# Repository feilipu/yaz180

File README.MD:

# YAZ180

There needed to be <strong>Yet Another Z180</strong> computer created.<br>
And so, here it is.

<div>
<table style="border: 2px solid #cccccc;">
<tbody>
<tr>
<td style="border: 1px solid #cccccc; padding: 6px;"></td>
</tr>
<tr>
<th style="border: 1px solid #cccccc; padding: 6px;"><centre>YAZ180 Version 2.4 2019 Left<center></th>
</tr>
<tr>
<td style="border: 1px solid #cccccc; padding: 6px;"></td>
</tr>
<tr>
<th style="border: 1px solid #cccccc; padding: 6px;"><centre>YAZ180 Version 2.4 2019 Right<center></th>
</tr>
<tr>
<td style="border: 1px solid #cccccc; padding: 6px;"></td>
</tr>
<tr>
<th style="border: 1px solid #cccccc; padding: 6px;"><centre>YAZ180 Version 2.1 2017 Live with YABIOS and CP/M<center></th>
</tr>
</tbody>
</table>
</div>

The [YAZ180](https://feilipu.me/?s=yaz180) is a modern single board computer, built on the tradition rich Z180 CPU and the AMD Am9511A-1 APU.

It is my attempt to create a perfect mix of "ancient" and  modern computing technology. Specifically, it is an attempt to marry CPU/APU technology from 40 years ago, with modern I2C, USB, and WiFi capabilities, and make an powerful 8-bit computer that can either be embedded into an application, or operate as a stand-alone computer (with some accessories).

The YAZ180 is supported by the Z88dk and it is designed to work with both traditional CP/M v2.2 applications and modern Z88dk C compiled programs.

The YAZ180 is fully open source. All documentation and design is available from this repository. I have made the raw PCBs available on [Tindie](https://www.tindie.com/products/feilipu/yaz180-pcb-modern-single-board-z180-computer/). I will find a way to get finished YAZ180 computers available shortly.

## Concept

The Z180 CPU is based on the Z80 CPU, but it includes a number of integrated peripherals including a basic Memory Management Unit (MMU), two serial interfaces (ASCI0 & ASCI1), two DMA controllers (DMAC0 & DMAC1), and two Programmable Reload Timers (PRT0 & PRT1).

The fastest readily available Flash memory is 55ns. This is matched by the fastest RAM in 8 x 1MByte packaging at 45ns. Using these two timings the fastest clock that can be therefore be supported is approximately 20MHz. Using this as a guide, and knowing that the Z180 ASCI interfaces are happiest running at a magic frequency, I have therefore selected 18.432MHz as the crystal oscillator frequency for the YAZ180.

The Z180 can operate internally at 2x the crystal oscillator frequency, which means that the YAZ180 is configured to run with PHI at 36.864MHz with 1 wait memory wait state in normal situations. This is slightly outside the Z180 specification (33MHz), but this frequency is reported to work without issues by a number of SBC builds.

The AMD Am9511A (1977) was the first hardware arithmetic Floating Point Unit (FPU) developed. It is essentially a "scientific calculator" on a chip, and is capable of both 16 bit and 32 bit fixed and 32 bit floating point processing, across all the standard and trancendental functions. Even though this device is 40 years old, it is still [comparable in performance](https://feilipu.me/2017/02/22/characterising-am9511a-1-apu/) of mathematical calculations to its Z180 host.

In addition to the internal Z180 interfaces, I have added a 82C55 Programmable Peripheral Interface (PPI) Controller (1974). This device provides 3x 8 bit parallel ports, and enables the YAZ180 to support 16bit IDE hard drives, as well as providing a mechanism to add parallel data interfacing to future expansion boards.

As the IDE interface requires control signals that are active low, several of the PPI Port C lines are passed through inverters. Importantly, those Port C lines that can accept input in PPI Mode 1 or Mode 2 are not inverted, and are therefore available as inputs from off-board applications. The IDE physical interface cable also provides a tidy board extension format, to allow extension or accessory devices to be attached to the YAZ180.

A single step circuitry has been implemented, which is enabled by a switch, and triggered by writing to an I/O port address. This enables the YAZ180 to run normally, until it becomes interesting to enable a breakpoint.

To interface with modern sensors and devices, two separate I2C interface PCA9665 devices have been provided. This enables one I2C device to be running at 1MHz in Fast-mode Plus (or even Turbo mode) driving a LCD controller for a screen (for example FTDI EVE), and have the other I2C interface connected over longer distances to sensors or keyboard running at 100kHz in Standard mode. The PCA9665 has deep 68 byte hardware buffers, and can operate in buffered or streaming mode, enabling complete I2C sentences to be transmitted or received without CPU interaction. A complete GL graphics command could be sent with one CPU DMA, for example.

To interface with TCP/IP networks, using WiFi, an ESP8266 pin-out for the ESP-01S is provided, connected to ASCI1. This enables the YAZ180 to operate as an Internet server (with attached IDE hard drive), and / or to be controlled using Secure Shell from anywhere.

A USB parallel interface is provided to enable "tool-less" programming of the YAZ180. A perl script is provided to upload Intel HEX code and program it into the system Flash memory. To enable this feature hardware is provided to reconfigure the memory map to allow boot from USB.

## PCB

The YAZ180 PCB is 160mm x 100mm in size, with 4 layers.<br>
This is the maximum size supported by the Eagle "Hobby Licence", which was used to create the PCB.

- Layer Top - all active devices (RED) - 2oz copper
- Layer 2 - GND layer (flood fill) - 0.5oz copper
- Layer 15 - VCC layer (flood fill) - 0.5oz copper
- Layer Bottom - signal traces (BLUE) - 2oz copper

- PCB Dimension - 160mm*100mm
- Material - FR-4 TG130
- Surface Finish - ENIG
- Min Solder Mask Dam - 0.4mm
- PCB Color - Black

<div>
<table style="border: 2px solid #cccccc;">
<tbody>
<tr>
<td style="border: 1px solid #cccccc; padding: 6px;"></td>
</tr>
<tr>
<th style="border: 1px solid #cccccc; padding: 6px;"><centre>YAZ180 Version 2.4 PCB 2019 Layout<center></th>
</tr>
<tr>
<td style="border: 1px solid #cccccc; padding: 6px;"></td>
</tr>
<tr>
<th style="border: 1px solid #cccccc; padding: 6px;"><centre>YAZ180 Version 2.1 PCB 2017<center></th>
</tr>
</tbody>
</table>
</div>

The YAZ180 requires 15V to 40V, 2A power supply, through a standard 2.1mm barrel jack.<br>
If you are not equipping the Am9511A-1 APU, then the minimum required supply voltage drops to 7V.

The main supply is switchmode rated at 5V 3A, which is used by most of the traditional devices on the board. Note that the <strong>TIL-311</strong> LED display devices consume approximately 105mA each, and operate <strong>HOT TO TOUCH</strong>.

A 3.3V 1A rated linear supply is fed from the 5V internal source. 3.3V is needed to support the I2C and ESP-01S devices.

The internal 12V 500mA rated switchmode supply is generated only to support the APU. Note that the <strong>Am9511A-1</strong> consumes 5V 70mA plus 12V 70mA normally, and operates <strong>BURNING HOT TO TOUCH</strong> (seriously).

The Z180 is supported by an ABT logic signal buffer on the /RD, /WR, /MREQ, and /IORQ lines, together with the four lowest address lines, A3, A2, A1, and A0. These signals are provided to all active elements, and so even though the Z180 includes its own signal buffers, I thought these signals should be additionally buffered.

The Z180 data lines are also buffered by an ABT logic bus transceiver. This is to ensure that these lines are also optimally driven.

## BOM

The <a href="https://github.com/feilipu/yaz180/blob/master/docs/YAZ180_V23_ListByValues.csv" target="_blank">Bill of Material</a> is available from DigiKey by modifying this [Shopping Cart](https://www.digikey.com.au/short/j103pz).

Note that there are two significant items missing from the Shopping Cart.

- The <a href="https://github.com/feilipu/yaz180/blob/master/docs/datasheets/Am9511%20Arithmetic%20Processor.pdf" target="_blank">Am9511A-1</a> is obsolete, and is only available from second tier chip sellers.
- The <a href="https://github.com/feilipu/yaz180/blob/master/docs/datasheets/til311.pdf" target="_blank">TIL-311</a> is not obsolete, but is no longer used in modern development and so is also not generally available.

Both of these products are readily available from second tier sources, but due to their scarcity they are not inexpensive.

Some other smaller pin-outs and connectors are not included:

- 2 of Seeed Studio Grove I2C connectors

## Memory & I/O Address Layout

The physical address mapping is provided by the standard CUPL (described below), and is completely arbitrary. Any other CUPL definitions can be programmed into the GAL16V8D "Memory" device to provide any memory layout desired.

### Physical Memory Address Space

The basic layout is to allow for an initial boot from flash memory into a BANK_0, with additional BANK_1 through BANK14 containing 64kB RAM based application spaces. The upper 4kB of each application space will be masked by COMMON AREA 1 RAM, which provides system utilities.

The additional flash memory is assigned to the upper memory space (BANK13, BANK14, and) BANK15, depending on the size of flash storage equipped. This non-volatile storage can be used for any purpose.

The PROGRAMMING MODE hardware recognises that data is available on the USB parallel port, and reconfigures the physical address mapping to enable boot from USB, and further programming of Flash or RAM.

<div>
<table style="border: 2px solid #cccccc;">
<tbody>
<tr>
<th style="border: 2px solid #cccccc; padding: 6px;">Physical Address Range</th>
<th style="border: 2px solid #cccccc; padding: 6px;">Run Mode</th>
<th style="border: 2px solid #cccccc; padding: 6px;">Programming Mode</th>
</tr>
<tr>
<th style="border: 1px solid #cccccc; padding: 6px;">$00000 - $0BFFF</th>
<td style="border: 1px solid #cccccc; padding: 6px;">Flash (48kB of 128kB)</td>
<td style="border: 1px solid #cccccc; padding: 6px;">USB pseudo RAM (48kB)</td>
</tr>
<tr>
<th style="border: 1px solid #cccccc; padding: 6px;">$0C000 - $DFFFF</th>
<td style="border: 1px solid #cccccc; padding: 6px;">SRAM (848kB of 1MB)</td>
<td style="border: 1px solid #cccccc; padding: 6px;">SRAM (848kB of 1MB)</td>
</tr>
<tr>
<th style="border: 1px solid #cccccc; padding: 6px;">$E0000 - $EFFFF</th>
<td style="border: 1px solid #cccccc; padding: 6px;">SRAM (64kB of 1MB)</td>
<td style="border: 1px solid #cccccc; padding: 6px;">Flash (64kB of 128kB)</td>
</tr>
<tr>
<th style="border: 1px solid #cccccc; padding: 6px;">$F0000 - $FFFFF</th>
<td style="border: 1px solid #cccccc; padding: 6px;">Flash (64kB of 128kB)</td>
<td style="border: 1px solid #cccccc; padding: 6px;">Flash (64kB of 128kB)</td>
</tr>
</tbody>
</table>
</div>

### Logical Memory Address Space

There is no need to follow this logical address space mapping. This is what I prefer. You can do whatever you want.

The organisation below is an attempt to provide a BANK_0 containing YABIOS (CRT0, boot code, and Z88dk library code) together with a RAM system heap. The COMMON AREA 1 space from 0xF000 to 0xFFFF is intended to hold banking code, system call forwarding, interrupt service routines, system buffers, and a system stack.

Additional BANK_1 through BANK14 are intended to hold user code, whether CP/M or Z88dk C programs, both are supported through system calls to BANK_0.

Flash found in (BANK13, BANK14, and) BANK15 is intended to be used for snapshots of default or frequently used applications. For example a CP/M snapshot would enable a "diskless" CP/M initialisation, using DMA to load within fractions of a second. Suggested default snapshots could be: CP/M CCP/BDOS, CP/M + BASIC, or Webserver, for example.

<div>
<table style="border: 2px solid #cccccc;">
<tbody>
<tr>
<th style="border: 2px solid #cccccc; padding: 6px;">Logical Address Range</th>
<th style="border: 2px solid #cccccc; padding: 6px;">Run Mode</th>
<th style="border: 2px solid #cccccc; padding: 6px;">Programming Mode</th>
</tr>
<tr>
<th style="border: 1px solid #cccccc; padding: 6px;">$0000 - $BFFF</th>
<td style="border: 1px solid #cccccc; padding: 6px;">Flash (48kB, BANK_0)</td>
<td style="border: 1px solid #cccccc; padding: 6px;">USB (48kB, CA0)</td>
</tr>
<tr>
<th style="border: 1px solid #cccccc; padding: 6px;">$C000 - $EFFF</th>
<td style="border: 1px solid #cccccc; padding: 6px;">SRAM (12kB, BANK_0)</td>
<td style="border: 1px solid #cccccc; padding: 6px;">Flash (8kB, BANK)</td>
</tr>
<tr>
<th style="border: 1px solid #cccccc; padding: 6px;">$F000 - $FFFF</th>
<td style="border: 1px solid #cccccc; padding: 6px;">SRAM (4kB, CA1)</td>
<td style="border: 1px solid #cccccc; padding: 6px;">SRAM (8kB, CA1)</td>
</tr>
</tbody>
</table>
</div>

### I/O Address Space

A computer always needs to be extended and to interact with the real world, and the YAZ180 provides multiple high-speed interfaces. As the Z180 supports 16 bit I/O addressing, the address lines A15-A13 to provide I/O selection options on the YAZ180.

Using a PLD to generate the I/O address mapping also allows flexibility to latch data into the Hex Display, or trigger breakpoints using Z180 #M1 and #Wait signals to allow Single Step execution from any code point.

<div>
<table style="border: 2px solid #cccccc;">
<tbody>
<tr>
<th style="border: 2px solid #cccccc; padding: 6px;">I/O Address Range</th>
<th style="border: 2px solid #cccccc; padding: 6px;">Chip Select (A15,A14,A13)</th>
<th style="border: 2px solid #cccccc; padding: 6px;">Device</th>
</tr>
<tr>
<th style="border: 1px solid #cccccc; padding: 6px;">$0000 - $1FFF</th>
<td style="border: 1px solid #cccccc; padding: 6px;">DO NOT USE</td>
<td style="border: 1px solid #cccccc; padding: 6px;">Internal I/O z180 #INTn $0000-$00FF Registers</td>
</tr>
<tr>
<th style="border: 1px solid #cccccc; padding: 6px;">$2000 - $3FFF</th>
<td style="border: 1px solid #cccccc; padding: 6px;">BREAK</td>
<td style="border: 1px solid #cccccc; padding: 6px;">Break Point - Initiate Single Step Mode</td>
</tr>
<tr>
<th style="border: 1px solid #cccccc; padding: 6px;">$4000 - $5FFF</th>
<td style="border: 1px solid #cccccc; padding: 6px;">#DIO_CS</td>
<td style="border: 1px solid #cccccc; padding: 6px;">82C55 $4000-$4003 Registers</span></td>
</tr>
<tr>
<th style="border: 1px solid #cccccc; padding: 6px;">$6000 - $7FFF</th>
<td style="border: 1px solid #cccccc; padding: 6px;">EXPANSION</td>
<td style="border: 1px solid #cccccc; padding: 6px;">Hold for Expansion</td>
</tr>
<tr>
<th style="border: 1px solid #cccccc; padding: 6px;">$8000 - $9FFF</th>
<td style="border: 1px solid #cccccc; padding: 6px;">#I2C_CS2</td>
<td style="border: 1px solid #cccccc; padding: 6px;">PCA9665 #INT2 $8000-$8003 Registers</td>
</tr>
<tr>
<th style="border: 1px solid #cccccc; padding: 6px;">$A000 - $BFFF</th>
<td style="border: 1px solid #cccccc; padding: 6px;">#I2C_CS1</td>
<td style="border: 1px solid #cccccc; padding: 6px;">PCA9665 #INT1 $A000-$A003 Registers</td>
</tr>
<tr>
<th style="border: 1px solid #cccccc; padding: 6px;">$C000 - $DFFF</th>
<td style="border: 1px solid #cccccc; padding: 6px;">#APU_CS</td>
<td style="border: 1px solid #cccccc; padding: 6px;">Am9511A-1 #INT0 $C000-$C001 Registers</td>
</tr>
<tr>
<th style="border: 1px solid #cccccc; padding: 6px;">$E000 - $FFFF</th>
<td style="border: 1px solid #cccccc; padding: 6px;">EXPANSION</td>
<td style="border: 1px solid #cccccc; padding: 6px;">Hold for Expansion</td>
</tr>
</tbody>
</table>
</div>

## CUPL

The YAZ180 is essentially software defined hardware. The use of Programmable Logic Devices (PLD) to control the board has enabled me to avoid multiple rework to repair issues, and has enabled reconfiguration of memory and I/O logic without raising a soldering iron.

### Memory GAL Configuration

### Logic (Single Step) GAL Configuration

The YAZ180 CUPL code is available in the [respective directory](https://github.com/feilipu/yaz180/tree/master/cupl).

## YABIOS

Please see here for the status of [YABIOS](https://github.com/feilipu/yaz180/tree/master/yabios).

Currently the YAZ180 is initialised to load preferably [YABIOS v1.1](https://github.com/feilipu/yaz180/tree/master/yabios) or alternatively [NASCOM Basic](https://github.com/feilipu/NASCOM_BASIC_4.7/tree/master/yaz180_NascomBasic56k). Applications can be built the [Z88dk]((https://github.com/z88dk/z88dk/tree/master/libsrc/_DEVELOPMENT/target/yaz180)) using the ROM (raw metal), and APP (yabios) models.

The YABIOS supports CP/M 2.2 Page 0 compatibility, with an underlying FAT32 File System, and has been extended to allow access to Z88dk libraries, and APU and floating point libraries, through the use of `RST+DEFW` short calls, and it includes both `_call_far` and `_jump_far` capability to allow applications to grow beyond 60kB. There is support for 16 MByte CP/M drives as FAT32 files on a Compact Flash or PATA IDE drive up to 128 Gbyte (LBA 28).

## Z88dk

[Z88dk support](https://github.com/z88dk/z88dk/tree/master/libsrc/_DEVELOPMENT/target/yaz180) has been completed, and improvement work continues daily.

## CP/M

CP/M is complete with console and teletype I/O, and the underlying disk sub-system working. Integration of CP/M disks as FAT32 files has also been completed. CP/M can be booted off the Flash snapshot and can load transient programs from FAT32 files (read as CP/M drives).

CP/M drive files can be read and written using a host PC with any operating system, by using the [`cpmtools`](http://www.moria.de/~michael/cpmtools/) utilities, simply by inserting the IDE drive in a USB drive caddy.

## Construction Notes

There are some [construction notes](https://github.com/feilipu/yaz180/tree/master/construction_notes.md) with errata, to advice on how to build the YAZ180.

## Owners Notes

There are some [owners notes](https://github.com/feilipu/yaz180/tree/master/owners_notes.md) advice on how to operate the YAZ180, and its environment.

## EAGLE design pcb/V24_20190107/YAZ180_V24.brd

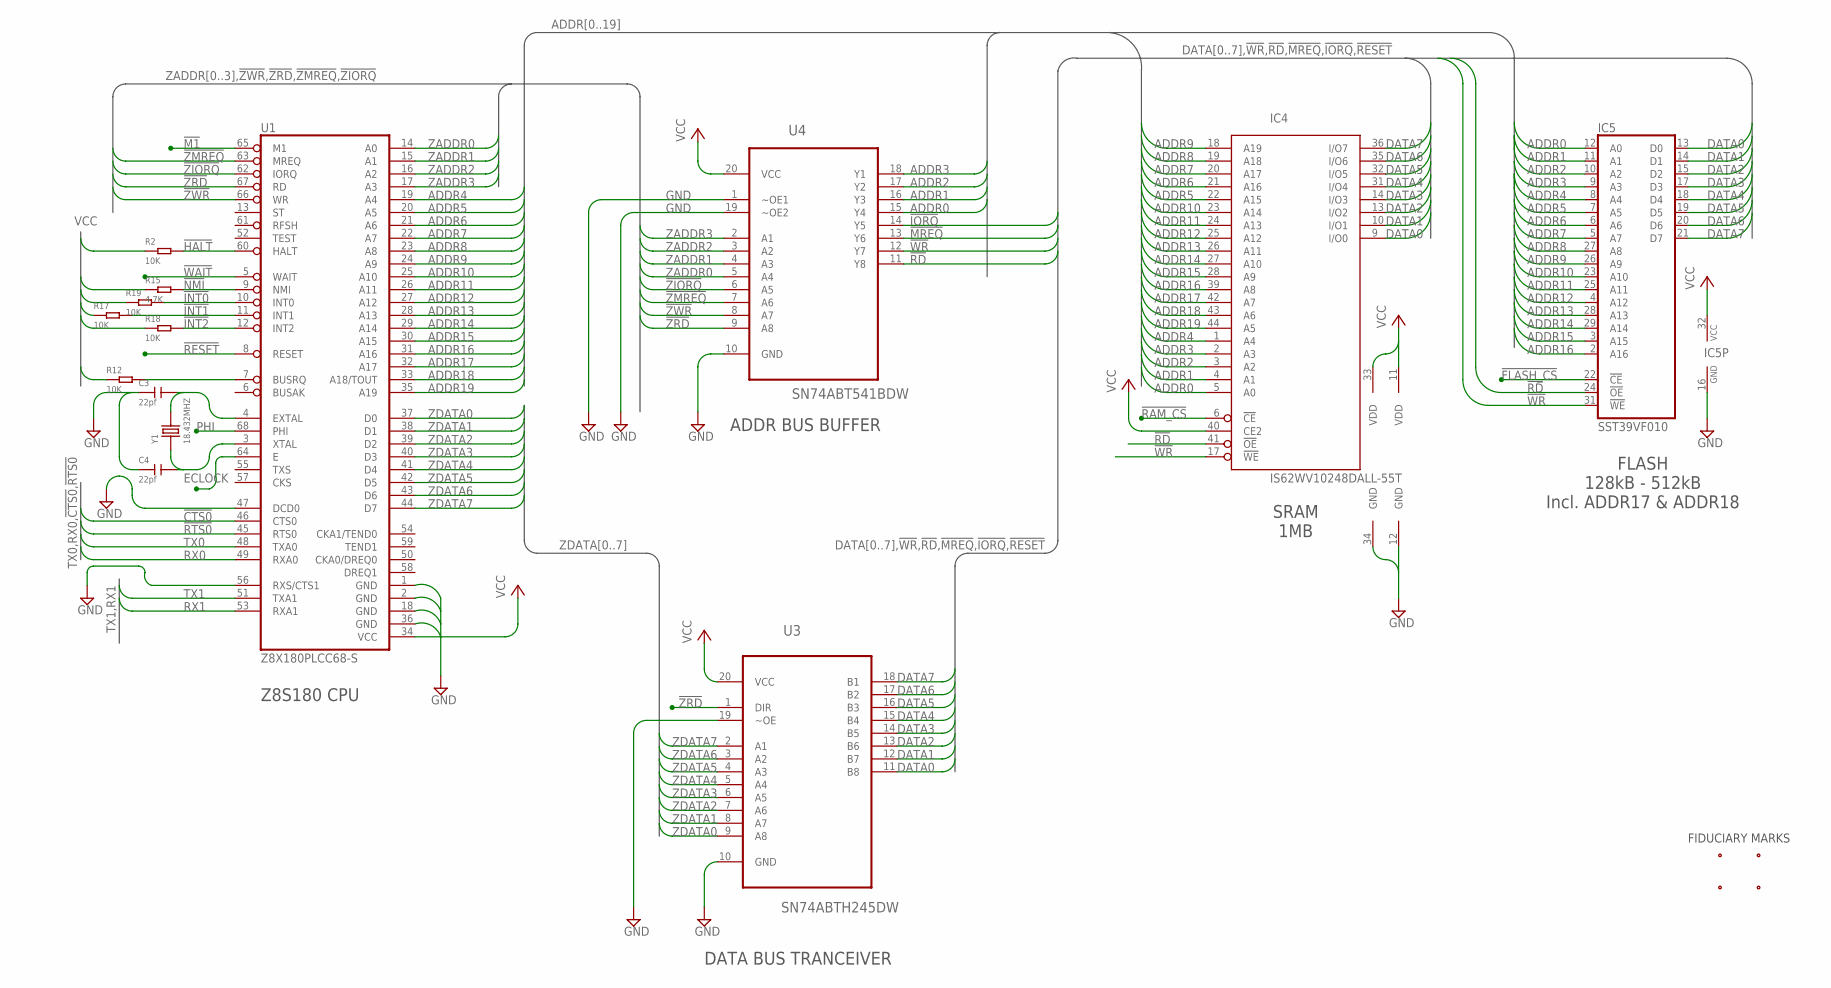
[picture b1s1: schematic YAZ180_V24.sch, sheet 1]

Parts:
C3, C4: 22pf; C0603
IC4: IS62WV10248DALL-55T; TSOP-II-44
IC5: SST39VF010; S32
R2, R12, R17, R18, R19: 10K; R0603
R15: 4.7K; R0603
U1: Z8X180PLCC68-S; PLCC-S68
U3: SN74ABTH245DW; SOIC127P1030X265-20N
U4: SN74ABT541BDW; SOIC127P1030X265-20N
X3, X4, X5, X6: FIDUCIAL_0.6-1.2MM; FIDUCIAL0.6-1.2
Y1: 18.432MHZ; HC49US

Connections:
!BUSRQ: R12.2, U1.7 (BUSRQ)
!CTS0: U1.46 (CTS0); also elsewhere on the board
!FLASH_CS: IC5.22 (!CE); also elsewhere on the board
!HALT: R2.2, U1.60 (HALT); also elsewhere on the board
!INT0: R19.2, U1.10 (INT0); also elsewhere on the board
!INT1: R17.2, U1.11 (INT1); also elsewhere on the board
!INT2: R18.2, U1.12 (INT2); also elsewhere on the board
!IORQ: U4.14 (Y5); also elsewhere on the board
!M1: U1.65 (M1); also elsewhere on the board
!MREQ: U4.13 (Y6); also elsewhere on the board
!NMI: R15.2, U1.9 (NMI)
!RAM_CS: IC4.6 (!CE); also elsewhere on the board
!RD: IC4.41 (!OE), IC5.24 (!OE), U4.11 (Y8); also elsewhere on the board
!RESET: U1.8 (RESET); also elsewhere on the board
!RTS0: U1.45 (RTS0); also elsewhere on the board
!WAIT: U1.5 (WAIT); also elsewhere on the board
!WR: IC4.17 (!WE), IC5.31 (!WE), U4.12 (Y7); also elsewhere on the board
!ZIORQ: U1.62 (IORQ), U4.6 (A5)
!ZMREQ: U1.63 (MREQ), U4.7 (A6)
!ZRD: U1.67 (RD), U3.1 (DIR), U4.9 (A8)
!ZWR: U1.66 (WR), U4.8 (A7); also elsewhere on the board
ADDR0: IC4.5 (A0), IC5.12 (A0), U4.15 (Y4); also elsewhere on the board
ADDR1: IC4.4 (A1), IC5.11 (A1), U4.16 (Y3); also elsewhere on the board
ADDR2: IC4.3 (A2), IC5.10 (A2), U4.17 (Y2); also elsewhere on the board
ADDR3: IC4.2 (A3), IC5.9 (A3), U4.18 (Y1); also elsewhere on the board
ADDR4: IC4.1 (A4), IC5.8 (A4), U1.19 (A4); also elsewhere on the board
ADDR5: IC4.22 (A15), IC5.7 (A5), U1.20 (A5); also elsewhere on the board
ADDR6: IC4.21 (A16), IC5.6 (A6), U1.21 (A6); also elsewhere on the board
ADDR7: IC4.20 (A17), IC5.5 (A7), U1.22 (A7); also elsewhere on the board
ADDR8: IC4.19 (A18), IC5.27 (A8), U1.23 (A8); also elsewhere on the board
ADDR9: IC4.18 (A19), IC5.26 (A9), U1.24 (A9); also elsewhere on the board
ADDR10: IC4.23 (A14), IC5.23 (A10), U1.25 (A10); also elsewhere on the board
ADDR11: IC4.24 (A13), IC5.25 (A11), U1.26 (A11); also elsewhere on the board
ADDR12: IC4.25 (A12), IC5.4 (A12), U1.27 (A12); also elsewhere on the board
ADDR13: IC4.26 (A11), IC5.28 (A13), U1.28 (A13); also elsewhere on the board
ADDR14: IC4.27 (A10), IC5.29 (A14), U1.29 (A14); also elsewhere on the board
ADDR15: IC4.28 (A9), IC5.3 (A15), U1.30 (A15); also elsewhere on the board
ADDR16: IC4.39 (A8), IC5.2 (A16), U1.31 (A16); also elsewhere on the board
ADDR17: IC4.42 (A7), U1.32 (A17); also elsewhere on the board
ADDR18: IC4.43 (A6), U1.33 (A18/TOUT); also elsewhere on the board
ADDR19: IC4.44 (A5), U1.35 (A19); also elsewhere on the board
DATA0: IC4.9 (I/O0), IC5.13 (D0), U3.11 (B8); also elsewhere on the board
DATA1: IC4.10 (I/O1), IC5.14 (D1), U3.12 (B7); also elsewhere on the board
DATA2: IC4.13 (I/O2), IC5.15 (D2), U3.13 (B6); also elsewhere on the board
DATA3: IC4.14 (I/O3), IC5.17 (D3), U3.14 (B5); also elsewhere on the board
DATA4: IC4.31 (I/O4), IC5.18 (D4), U3.15 (B4); also elsewhere on the board
DATA5: IC4.32 (I/O5), IC5.19 (D5), U3.16 (B3); also elsewhere on the board
DATA6: IC4.35 (I/O6), IC5.20 (D6), U3.17 (B2); also elsewhere on the board
DATA7: IC4.36 (I/O7), IC5.21 (D7), U3.18 (B1); also elsewhere on the board
ECLOCK: U1.64 (E); also elsewhere on the board
EXTAL: C3.2, U1.4 (EXTAL), Y1.2
GND: C3.1, C4.1, IC4.12 (GND), IC4.34 (GND), IC5.16 (GND), U1.1 (GND), U1.2 (GND), U1.18 (GND), U1.36 (GND), U1.47 (DCD0), U1.56 (RXS/CTS1), U3.10 (GND), U3.19 (~OE), U4.1 (~OE1), U4.10 (GND), U4.19 (~OE2); also elsewhere on the board
PHI: U1.68 (PHI); also elsewhere on the board
RX0: U1.49 (RXA0); also elsewhere on the board
RX1: U1.53 (RXA1); also elsewhere on the board
TX0: U1.48 (TXA0); also elsewhere on the board
TX1: U1.51 (TXA1); also elsewhere on the board
VCC: IC4.11 (VDD), IC4.33 (VDD), IC4.40 (CE2), IC5.32 (VCC), R2.1, R12.1, R15.1, R17.1, R18.1, R19.1, U1.34 (VCC), U3.20 (VCC), U4.20 (VCC); also elsewhere on the board
XTAL: C4.2, U1.3 (XTAL), Y1.1
ZADDR0: U1.14 (A0), U4.5 (A4)
ZADDR1: U1.15 (A1), U4.4 (A3)
ZADDR2: U1.16 (A2), U4.3 (A2)
ZADDR3: U1.17 (A3), U4.2 (A1)
ZDATA0: U1.37 (D0), U3.9 (A8)
ZDATA1: U1.38 (D1), U3.8 (A7)
ZDATA2: U1.39 (D2), U3.7 (A6)
ZDATA3: U1.40 (D3), U3.6 (A5)
ZDATA4: U1.41 (D4), U3.5 (A4)
ZDATA5: U1.42 (D5), U3.4 (A3)
ZDATA6: U1.43 (D6), U3.3 (A2)
ZDATA7: U1.44 (D7), U3.2 (A1)

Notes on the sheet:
FIDUCIARY MARKS
Z8S180 CPU
ADDR BUS BUFFER
SRAM 1MB
FLASH 128kB - 512kB Incl. ADDR17 & ADDR18
DATA BUS TRANCEIVER

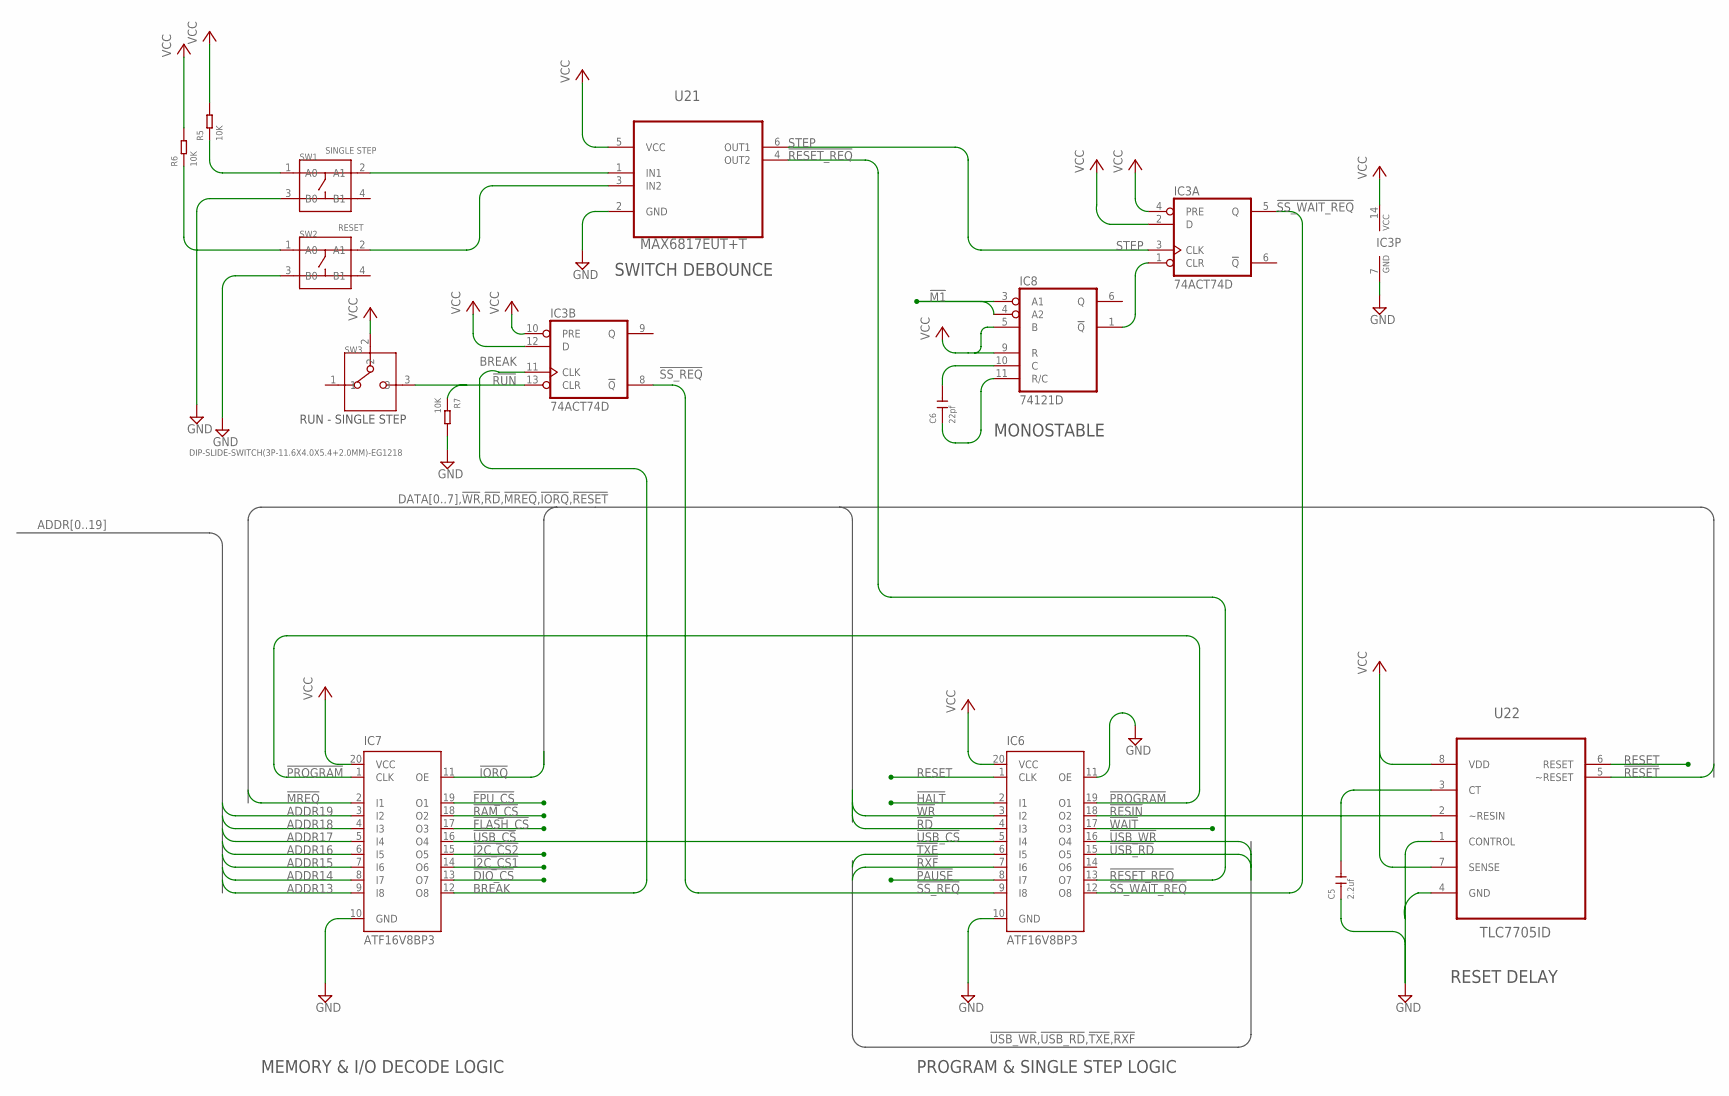
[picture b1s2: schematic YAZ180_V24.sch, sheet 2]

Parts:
C5: 2.2uf; C0603
C6: 22pf; C0603
IC3: 74ACT74D; SO14
IC6, IC7: ATF16V8BP3; DIL20
IC8: 74121D; SO14
R5, R6, R7: 10K; R0603
SW1: SINGLE STEP; SW4-SMD-4.0X4.0X1.7MM
SW2: RESET; SW4-SMD-4.0X4.0X1.7MM
SW3: DIP-SLIDE-SWITCH(3P-11.6X4.0X5.4+2.0MM)-EG1218; SW3-2.5-11.6X4.0X5.4+2.0MM
U21: MAX6817EUT+T; SOT95P280X145-6N
U22: TLC7705ID; SOIC127P600X175-8N

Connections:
!DIO_CS: IC7.13 (O7); also elsewhere on the board
!FLASH_CS: IC7.17 (O3); also elsewhere on the board
!FPU_CS: IC7.19 (O1); also elsewhere on the board
!HALT: IC6.2 (I1); also elsewhere on the board
!I2C_CS1: IC7.14 (O6); also elsewhere on the board
!I2C_CS2: IC7.15 (O5); also elsewhere on the board
!IORQ: IC7.11 (OE); also elsewhere on the board
!M1: IC8.3 (A1), IC8.4 (A2); also elsewhere on the board
!MREQ: IC7.2 (I1); also elsewhere on the board
!PAUSE: IC6.8 (I7); also elsewhere on the board
!PROGRAM: IC6.19 (O1), IC7.1 (CLK)
!RAM_CS: IC7.18 (O2); also elsewhere on the board
!RD: IC6.4 (I3); also elsewhere on the board
!RESET: U22.5 (~RESET); also elsewhere on the board
!RESET_REQ: IC6.13 (O7), U21.4 (OUT2)
!RESIN: IC6.18 (O2), U22.2 (~RESIN)
!RUN: IC3.13 (CLR), R7.1, SW3.3
!RXF: IC6.7 (I6); also elsewhere on the board
!SS_REQ: IC3.8 (!Q), IC6.9 (I8)
!SS_WAIT_REQ: IC3.5 (Q), IC6.12 (O8)
!TXE: IC6.6 (I5); also elsewhere on the board
!USB_CS: IC6.5 (I4), IC7.16 (O4)
!USB_RD: IC6.15 (O5); also elsewhere on the board
!USB_WR: IC6.16 (O4); also elsewhere on the board
!WAIT: IC6.17 (O3); also elsewhere on the board
!WR: IC6.3 (I2); also elsewhere on the board
ADDR13: IC7.9 (I8); also elsewhere on the board
ADDR14: IC7.8 (I7); also elsewhere on the board
ADDR15: IC7.7 (I6); also elsewhere on the board
ADDR16: IC7.6 (I5); also elsewhere on the board
ADDR17: IC7.5 (I4); also elsewhere on the board
ADDR18: IC7.4 (I3); also elsewhere on the board
ADDR19: IC7.3 (I2); also elsewhere on the board
BREAK: IC3.11 (CLK), IC7.12 (O8)
GND: C5.1, IC3.7 (GND), IC6.10 (GND), IC6.11 (OE), IC7.10 (GND), IC8.7 (GND), R7.2, SW1.3 (B0), SW2.3 (B0), U21.2 (GND), U22.1 (CONTROL), U22.4 (GND); also elsewhere on the board
unnamed: IC3.1 (CLR), IC8.1 (!Q)
unnamed: C5.2, U22.3 (CT)
unnamed: C6.2, IC8.10 (C)
unnamed: SW1.2 (A1), U21.1 (IN1)
unnamed: R5.1, SW1.1 (A0)
unnamed: R6.1, SW2.1 (A0)
unnamed: SW2.2 (A1), U21.3 (IN2)
unnamed: C6.1, IC8.11 (R/C)
RESET: IC6.1 (CLK), U22.6 (RESET); also elsewhere on the board
STEP: IC3.3 (CLK), U21.6 (OUT1)
VCC: IC3.2 (D), IC3.4 (PRE), IC3.10 (PRE), IC3.12 (D), IC3.14 (VCC), IC6.20 (VCC), IC7.20 (VCC), IC8.5 (B), IC8.9 (R), IC8.14 (VCC), R5.2, R6.2, SW3.2, U21.5 (VCC), U22.7 (SENSE), U22.8 (VDD); also elsewhere on the board

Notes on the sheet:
RUN - SINGLE STEP
SWITCH DEBOUNCE
MEMORY & I/O DECODE LOGIC
PROGRAM & SINGLE STEP LOGIC
RESET DELAY
MONOSTABLE

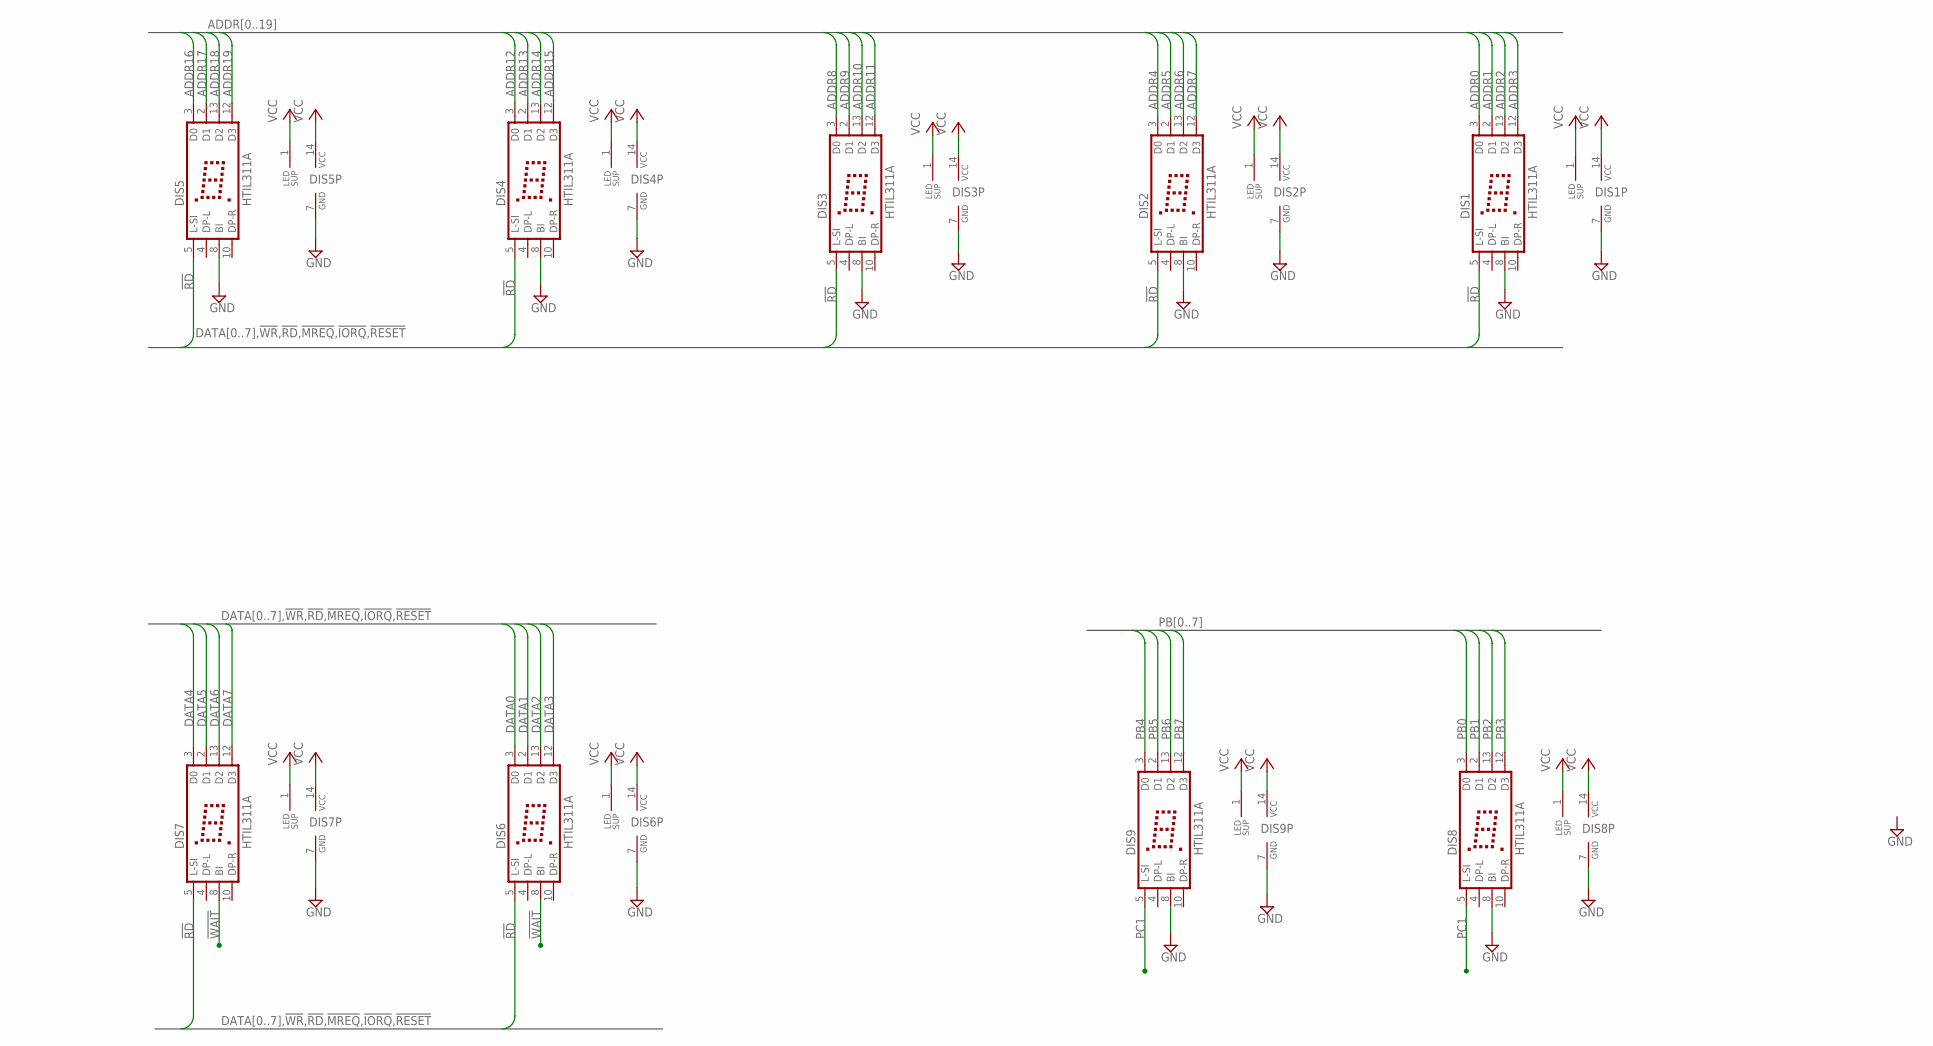
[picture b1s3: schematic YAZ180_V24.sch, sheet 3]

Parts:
DIS1, DIS2, DIS3, DIS4, DIS5, DIS6, DIS7, DIS8, DIS9: HTIL311A

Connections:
!RD: DIS1.5 (L-SI), DIS2.5 (L-SI), DIS3.5 (L-SI), DIS4.5 (L-SI), DIS5.5 (L-SI), DIS6.5 (L-SI), DIS7.5 (L-SI); also elsewhere on the board
!WAIT: DIS6.8 (BI), DIS7.8 (BI); also elsewhere on the board
ADDR0: DIS1.3 (D0); also elsewhere on the board
ADDR1: DIS1.2 (D1); also elsewhere on the board
ADDR2: DIS1.13 (D2); also elsewhere on the board
ADDR3: DIS1.12 (D3); also elsewhere on the board
ADDR4: DIS2.3 (D0); also elsewhere on the board
ADDR5: DIS2.2 (D1); also elsewhere on the board
ADDR6: DIS2.13 (D2); also elsewhere on the board
ADDR7: DIS2.12 (D3); also elsewhere on the board
ADDR8: DIS3.3 (D0); also elsewhere on the board
ADDR9: DIS3.2 (D1); also elsewhere on the board
ADDR10: DIS3.13 (D2); also elsewhere on the board
ADDR11: DIS3.12 (D3); also elsewhere on the board
ADDR12: DIS4.3 (D0); also elsewhere on the board
ADDR13: DIS4.2 (D1); also elsewhere on the board
ADDR14: DIS4.13 (D2); also elsewhere on the board
ADDR15: DIS4.12 (D3); also elsewhere on the board
ADDR16: DIS5.3 (D0); also elsewhere on the board
ADDR17: DIS5.2 (D1); also elsewhere on the board
ADDR18: DIS5.13 (D2); also elsewhere on the board
ADDR19: DIS5.12 (D3); also elsewhere on the board
DATA0: DIS6.3 (D0); also elsewhere on the board
DATA1: DIS6.2 (D1); also elsewhere on the board
DATA2: DIS6.13 (D2); also elsewhere on the board
DATA3: DIS6.12 (D3); also elsewhere on the board
DATA4: DIS7.3 (D0); also elsewhere on the board
DATA5: DIS7.2 (D1); also elsewhere on the board
DATA6: DIS7.13 (D2); also elsewhere on the board
DATA7: DIS7.12 (D3); also elsewhere on the board
GND: DIS1.7 (GND), DIS1.8 (BI), DIS2.7 (GND), DIS2.8 (BI), DIS3.7 (GND), DIS3.8 (BI), DIS4.7 (GND), DIS4.8 (BI), DIS5.7 (GND), DIS5.8 (BI), DIS6.7 (GND), DIS7.7 (GND), DIS8.7 (GND), DIS8.8 (BI), DIS9.7 (GND), DIS9.8 (BI); also elsewhere on the board
PB0: DIS8.3 (D0); also elsewhere on the board
PB1: DIS8.2 (D1); also elsewhere on the board
PB2: DIS8.13 (D2); also elsewhere on the board
PB3: DIS8.12 (D3); also elsewhere on the board
PB4: DIS9.3 (D0); also elsewhere on the board
PB5: DIS9.2 (D1); also elsewhere on the board
PB6: DIS9.13 (D2); also elsewhere on the board
PB7: DIS9.12 (D3); also elsewhere on the board
PC1: DIS8.5 (L-SI), DIS9.5 (L-SI); also elsewhere on the board
VCC: DIS1.1 (LEDSUP), DIS1.14 (VCC), DIS2.1 (LEDSUP), DIS2.14 (VCC), DIS3.1 (LEDSUP), DIS3.14 (VCC), DIS4.1 (LEDSUP), DIS4.14 (VCC), DIS5.1 (LEDSUP), DIS5.14 (VCC), DIS6.1 (LEDSUP), DIS6.14 (VCC), DIS7.1 (LEDSUP), DIS7.14 (VCC), DIS8.1 (LEDSUP), DIS8.14 (VCC), DIS9.1 (LEDSUP), DIS9.14 (VCC); also elsewhere on the board

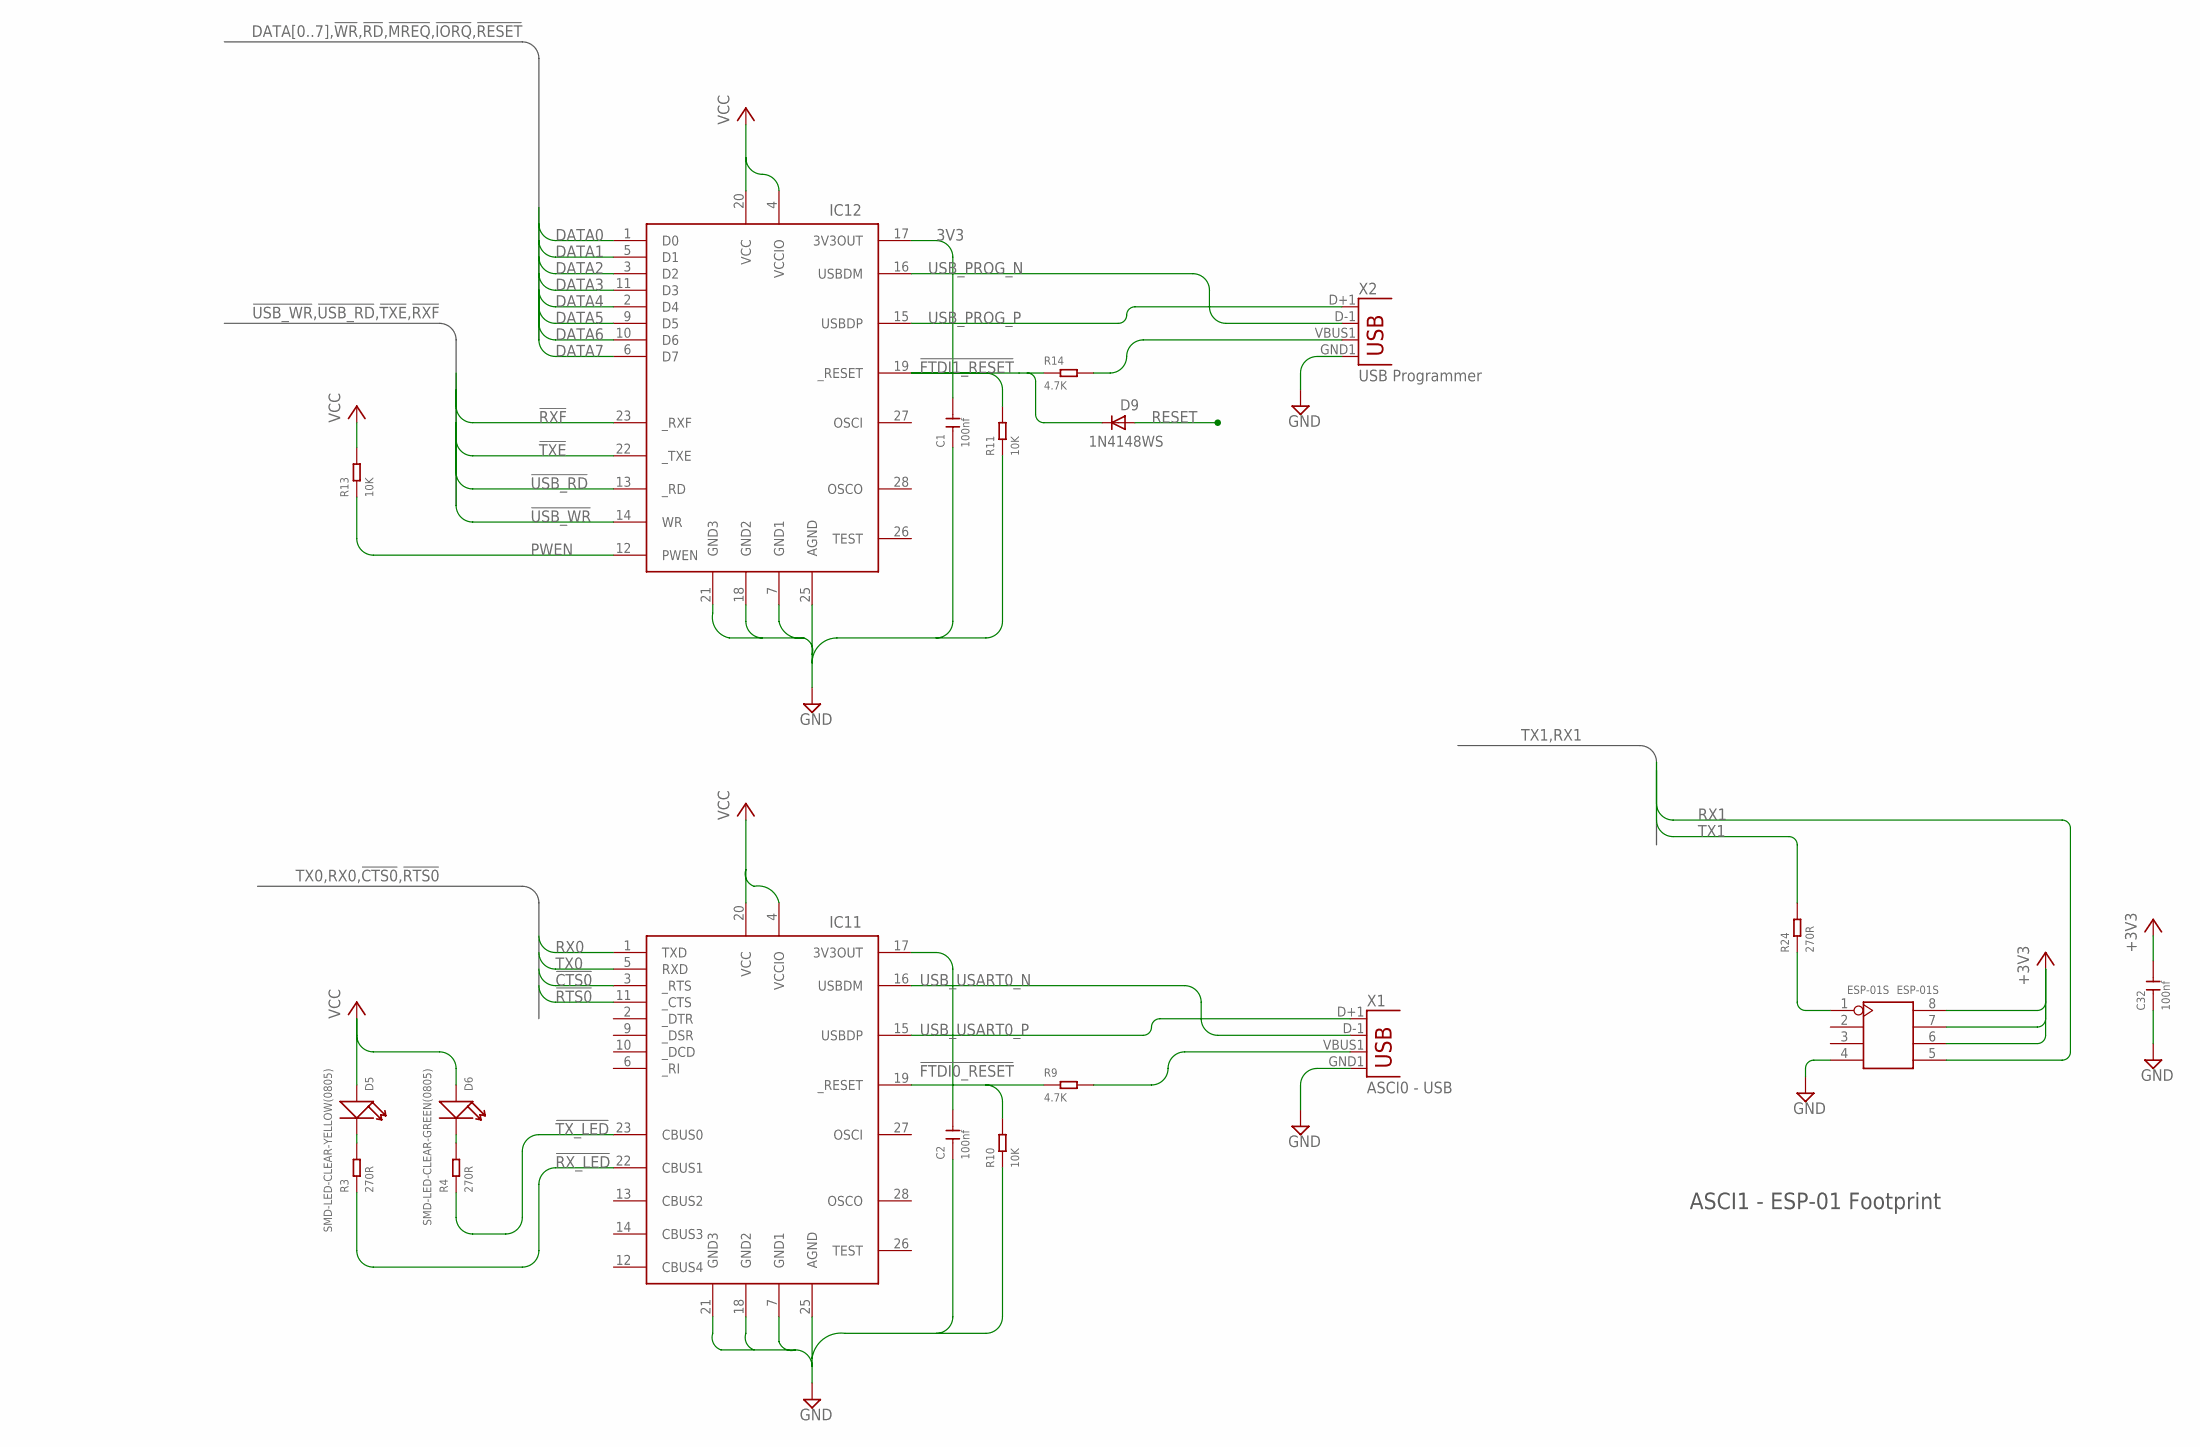
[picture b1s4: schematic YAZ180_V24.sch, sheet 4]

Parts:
C1, C2, C32: 100nf; C0603
D5: SMD-LED-CLEAR-YELLOW(0805); LED-0805
D6: SMD-LED-CLEAR-GREEN(0805); LED-0805
D9: 1N4148WS; SOD323F
ESP-01S: ESP-01S; H2X4-2.54
IC11: FT232RL; SSOP28DB
IC12: FT245RL; SSOP28DB
R3, R4, R24: 270R; R0603
R9, R14: 4.7K; R0603
R10, R11, R13: 10K; R0603
X1: ASCI0 - USB; USB-A-SMT-MALE
X2: USB Programmer; USB-A-SMT-MALE

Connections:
3V3: C1.2, IC12.17 (3V3OUT)
!CTS0: IC11.3 (_RTS); also elsewhere on the board
!FTDI0_RESET: IC11.19 (_RESET), R9.1, R10.2
!FTDI1_RESET: D9.C, IC12.19 (_RESET), R11.2, R14.1
!RTS0: IC11.11 (_CTS); also elsewhere on the board
!RXF: IC12.23 (_RXF); also elsewhere on the board
!RX_LED: IC11.22 (CBUS1), R3.1
!TXE: IC12.22 (_TXE); also elsewhere on the board
!TX_LED: IC11.23 (CBUS0), R4.1
!USB_RD: IC12.13 (_RD); also elsewhere on the board
!USB_WR: IC12.14 (WR); also elsewhere on the board
+3V3: C32.2, ESP-01S.6, ESP-01S.7, ESP-01S.8; also elsewhere on the board
DATA0: IC12.1 (D0); also elsewhere on the board
DATA1: IC12.5 (D1); also elsewhere on the board
DATA2: IC12.3 (D2); also elsewhere on the board
DATA3: IC12.11 (D3); also elsewhere on the board
DATA4: IC12.2 (D4); also elsewhere on the board
DATA5: IC12.9 (D5); also elsewhere on the board
DATA6: IC12.10 (D6); also elsewhere on the board
DATA7: IC12.6 (D7); also elsewhere on the board
GND: C1.1, C2.1, C32.1, ESP-01S.4, IC11.7 (GND1), IC11.18 (GND2), IC11.21 (GND3), IC11.25 (AGND), IC12.7 (GND1), IC12.18 (GND2), IC12.21 (GND3), IC12.25 (AGND), R10.1, R11.1, X1.GND1 (GND), X2.GND1 (GND); also elsewhere on the board
unnamed: R14.2, X2.VBUS1 (VBUS)
unnamed: R9.2, X1.VBUS1 (VBUS)
unnamed: ESP-01S.1, R24.1
unnamed: C2.2, IC11.17 (3V3OUT)
unnamed: D5.-, R3.2
unnamed: D6.-, R4.2
PWEN: IC12.12 (PWEN), R13.1
RESET: D9.A; also elsewhere on the board
RX0: IC11.1 (TXD); also elsewhere on the board
RX1: ESP-01S.5; also elsewhere on the board
TX0: IC11.5 (RXD); also elsewhere on the board
TX1: R24.2; also elsewhere on the board
USB_PROG_N: IC12.16 (USBDM), X2.D-1 (D-)
USB_PROG_P: IC12.15 (USBDP), X2.D+1 (D+)
USB_USART0_N: IC11.16 (USBDM), X1.D-1 (D-)
USB_USART0_P: IC11.15 (USBDP), X1.D+1 (D+)
VCC: D5.+, D6.+, IC11.4 (VCCIO), IC11.20 (VCC), IC12.4 (VCCIO), IC12.20 (VCC), R13.2; also elsewhere on the board

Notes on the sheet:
ASCI1 - ESP-01 Footprint

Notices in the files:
parts and their libraries:
SparkFun-Connectors: Licensing: Creative Commons ShareAlike 4.0 International - https://creativecommons.org/licenses/by-sa/4.0
